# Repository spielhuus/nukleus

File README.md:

<p align="left">

</p>

# nukleus
Nukleus is a continuous integration and simulation tool for electronics projects.

# dependencies

install dependencies on debian/ubuntu

```
apt-get install build-essential pkg-config
apt-get install libgirepository1.0-dev libcairo2-dev libpango1.0-dev
```

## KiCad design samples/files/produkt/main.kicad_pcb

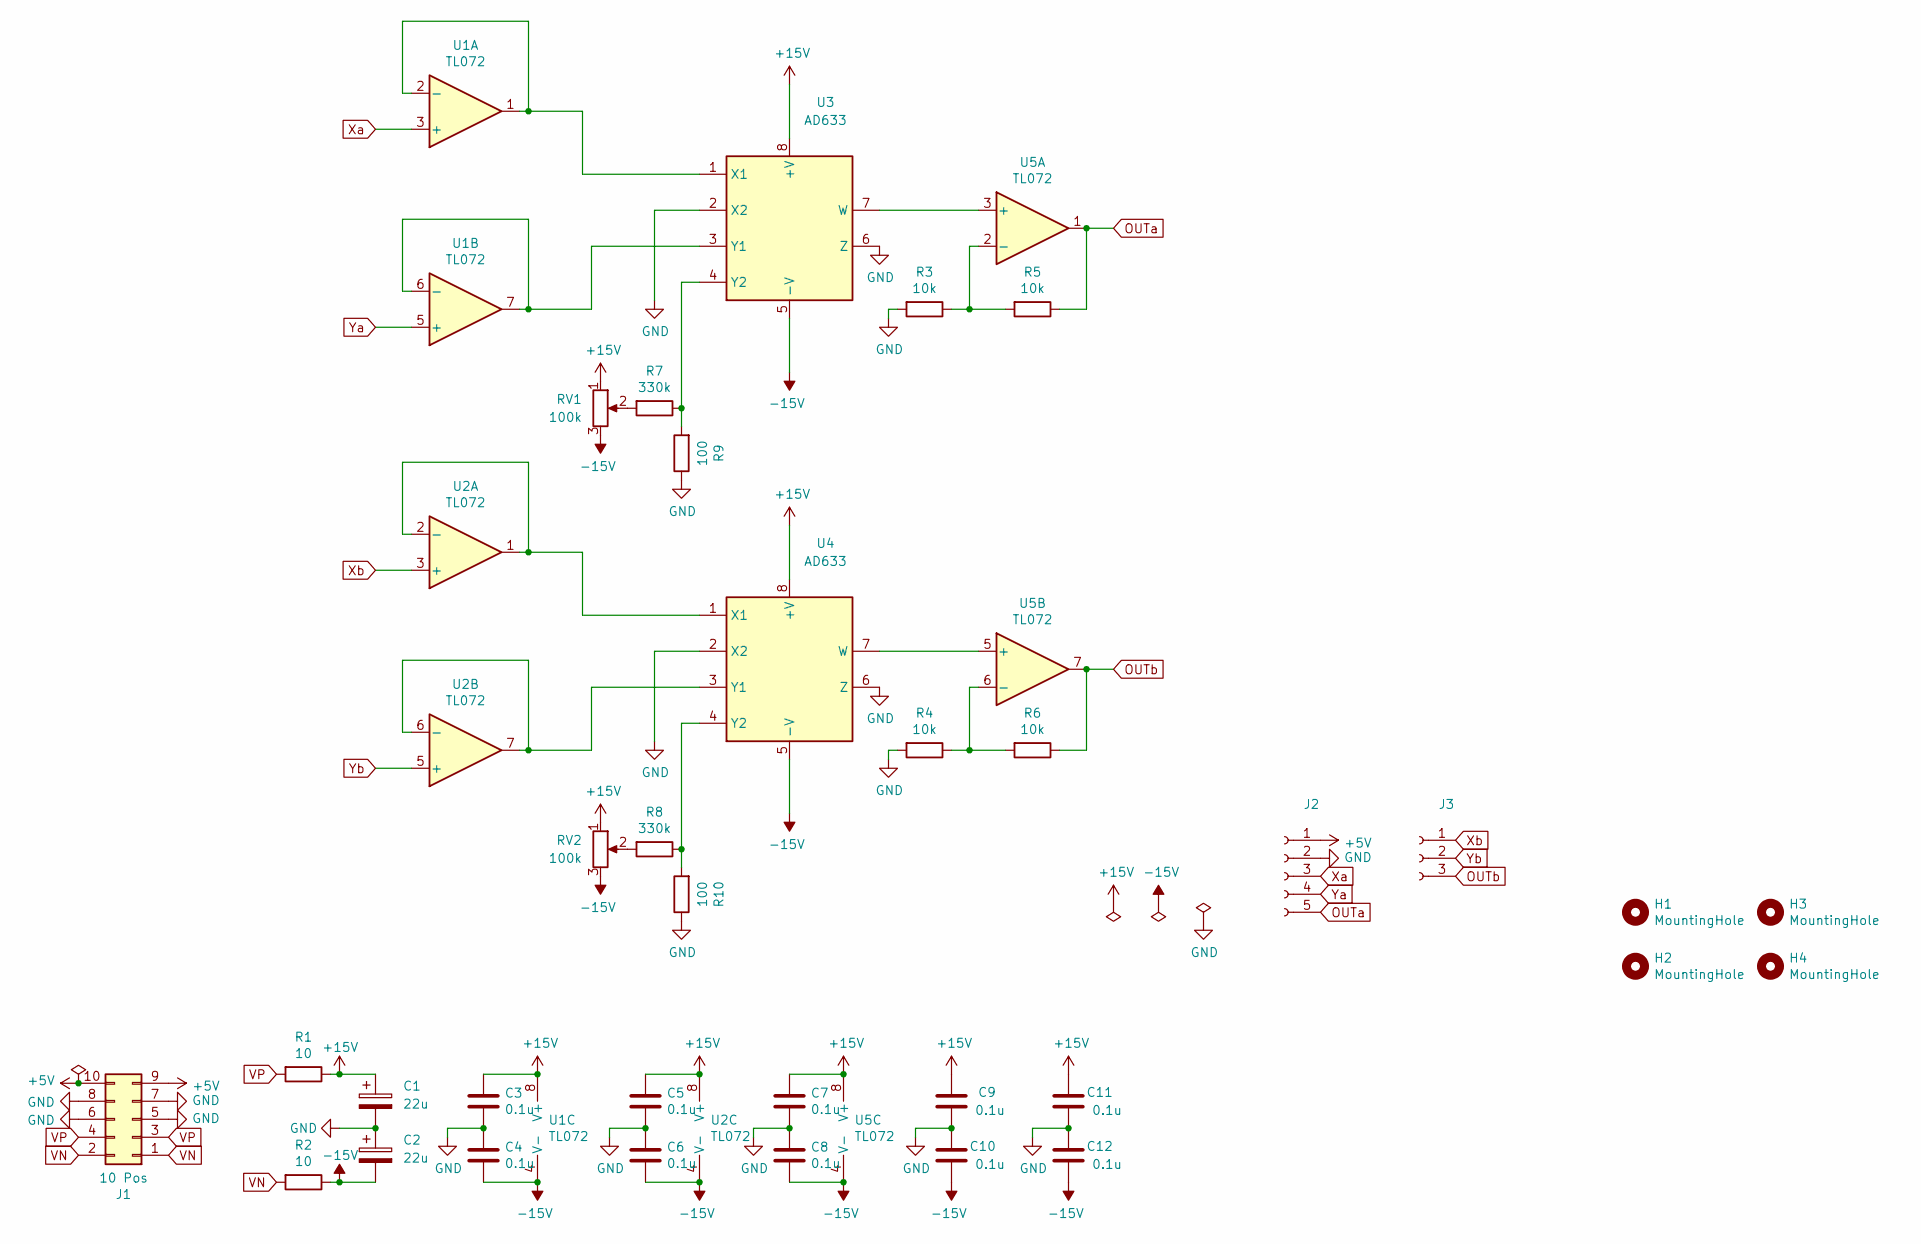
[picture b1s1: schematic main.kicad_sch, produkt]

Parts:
C1, C2: 22u; CP_Radial_D6.3mm_P2.50mm
C3, C4, C5, C6, C7, C8, C9, C10, C11, C12: 0.1u; C_Disc_D3.4mm_W2.1mm_P2.50mm
H1, H2, H3, H4: MountingHole; MountingHole_2.2mm_M2
J1: 10 Pos; IDC-Header_2x05_P2.54mm_Vertical
J2: 01x05 Female; PinSocket_1x05_P2.54mm_Vertical
J3: 01x03 Female; PinSocket_1x03_P2.54mm_Vertical
R1, R2: 10; R_Axial_DIN0204_L3.6mm_D1.6mm_P5.08mm_Horizontal
R3, R4, R5, R6: 10k; R_Axial_DIN0204_L3.6mm_D1.6mm_P5.08mm_Horizontal
R7, R8: 330k; R_Axial_DIN0204_L3.6mm_D1.6mm_P5.08mm_Horizontal
R9, R10: 100; R_Axial_DIN0204_L3.6mm_D1.6mm_P5.08mm_Horizontal
RV1, RV2: 100k
U1, U2, U5: TL072; DIP-8_W7.62mm_Socket
U3, U4: AD633; DIP-8_W7.62mm

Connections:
+5V: J1.9, J1.10, J2.1
+15V: C1.1, C3.1, C5.1, C7.1, C9.1, C11.1, R1.1, RV1.1, RV2.1, U1.8 (V+), U2.8 (V+), U3.8 (+V), U4.8 (+V), U5.8 (V+)
-15V: C2.2, C4.2, C6.2, C8.2, C10.2, C12.2, R2.1, RV1.3, RV2.3, U1.4 (V-), U2.4 (V-), U3.5 (-V), U4.5 (-V), U5.4 (V-)
GND: C1.2, C2.1, C3.2, C4.1, C5.2, C6.1, C7.2, C8.1, C9.2, C10.1, C11.2, C12.1, J1.5, J1.6, J1.7, J1.8, J2.2, R3.2, R4.2, R9.1, R10.1, U3.2 (X2), U3.6 (Z), U4.2 (X2), U4.6 (Z)
unnamed: R3.1, R5.2, U5.2 (-)
unnamed: R4.1, R6.2, U5.6 (-)
unnamed: R7.1, R9.2, U3.4 (Y2)
unnamed: R7.2, RV1.2
unnamed: R8.2, RV2.2
unnamed: R8.1, R10.2, U4.4 (Y2)
unnamed: U1.1, U1.2 (-), U3.1 (X1)
unnamed: U1.6 (-), U1.7, U3.3 (Y1)
unnamed: U2.1, U2.2 (-), U4.1 (X1)
unnamed: U2.6 (-), U2.7, U4.3 (Y1)
unnamed: U3.7 (W), U5.3 (+)
unnamed: U4.7 (W), U5.5 (+)
OUTa: J2.5, R5.1, U5.1
OUTb: J3.3, R6.1, U5.7
VN: J1.1, J1.2, R2.2
VP: J1.3, J1.4, R1.2
Xa: J2.3, U1.3 (+)
Xb: J3.1, U2.3 (+)
Ya: J2.4, U1.5 (+)
Yb: J3.2, U2.5 (+)

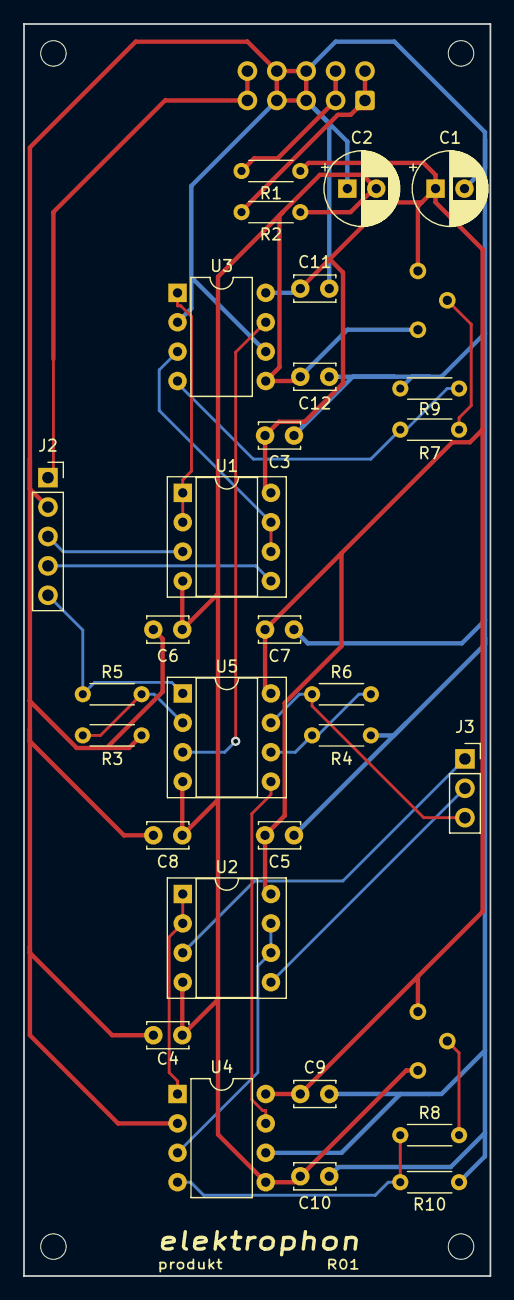
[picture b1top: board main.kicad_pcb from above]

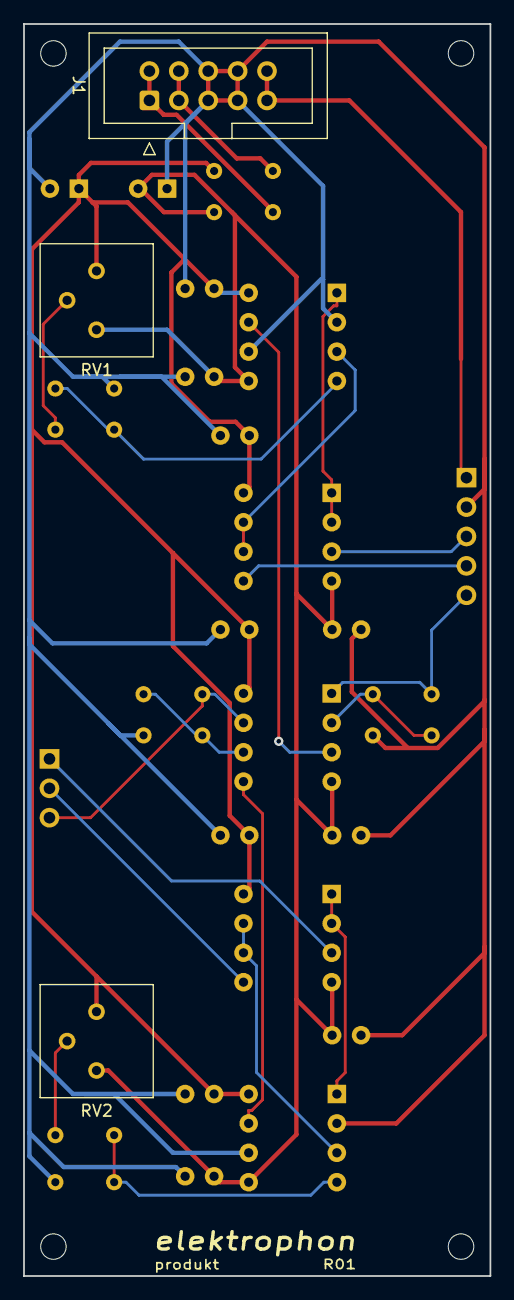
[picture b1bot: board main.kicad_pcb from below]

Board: 2 copper layers, 40.3 x 108.2 mm, 36 parts (3 on the bottom side), 24 nets.

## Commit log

2022-02-13 initial project import
2022-02-14 add documentation
2022-02-19 update model
2022-02-20 remove autosummary
2022-02-21 reintegrate code against model
2022-02-24 plot refactoring
2022-02-25 calculate Plot outline
2022-02-26 calculate Plot outlines and justify
2022-02-26 TextEffect face default value
2022-02-27 add scons and jupyter
2022-02-28 fix floating point issue
2022-02-28 Add .deepsource.toml
2022-03-03 add bom and erc
2022-03-03 add dockerfile
2022-03-03 update bom
2022-03-06 update makefile and integrate pcbnew
2022-03-06 report generation
2022-03-06 report keys
2022-03-06 group bom results
2022-03-06 add main entrypoint
2022-03-06 update logger
2022-03-06 update main
2022-03-08 update Plot
2022-03-09 add A3 page size
2022-03-09 add scale factor
2022-03-19 update code and cleanup
2022-03-19 refactor
2022-03-19 load _pcbnew
2022-03-19 add dependencies
2022-03-19 assert number
2022-03-27 add yabs configuration
2022-04-02 parse kicad pcb files
2022-04-05 parse kicad PCB file
2022-04-08 fix draw to model
2022-04-09 add element tox and toy
2022-04-09 fix unit tests
2022-04-09 update spice and netlist
2022-04-10 update draw and notebook theme
2022-04-11 code cleanup
2022-04-11 calculate stroke in plot
2022-04-11 ngspice transient parameters
2022-04-11 output svg buffer
2022-04-11 clean svg buffer
2022-04-12 single field position
2022-04-12 clean draw implementation
2022-04-12 clean plot implementation
2022-04-12 place fields
2022-04-12 circuit and add potentiometer
2022-04-12 add operating point analysis
2022-04-12 getattr on circuit
2022-04-12 show netlist in diagram
2022-04-12 correct left and right
2022-04-13 correct netlist calculation
2022-04-13 add diode in circuit
2022-04-13 update text placement
2022-04-14 add osifont
2022-04-14 update header text placement
2022-04-14 radian in draw circle
2022-04-15 update draw base
2022-05-15 schema refactoring
2022-05-16 update scons files
2022-05-16 add reference method
2022-05-16 check items in title block
2022-05-16 add networkx
2022-05-21 extend schema parser
2022-05-21 update netlist creation
2022-05-21 refactor scons builders
2022-05-21 refactor samples and tests
2022-05-21 extend ERC
2022-05-23 update schema code and add notebook
2022-06-12 update python code

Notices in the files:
samples/files/produkt/main.kicad_pcb:
License CC BY 4.0 - Attribution 4.0 International
